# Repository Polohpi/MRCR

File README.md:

# MRCR
Banc de Rodage pour moteur Nitro

Arduino SAMD21 M0

using :

PID_v1 library            https://github.com/br3ttb/Arduino-PID-Library
Scheduler                 https://github.com/arduino-libraries/Scheduler
Easy Nextion Library      https://github.com/Seithan/EasyNextionLibrary
MovingAvg                  https://github.com/JChristensen/movingAvg

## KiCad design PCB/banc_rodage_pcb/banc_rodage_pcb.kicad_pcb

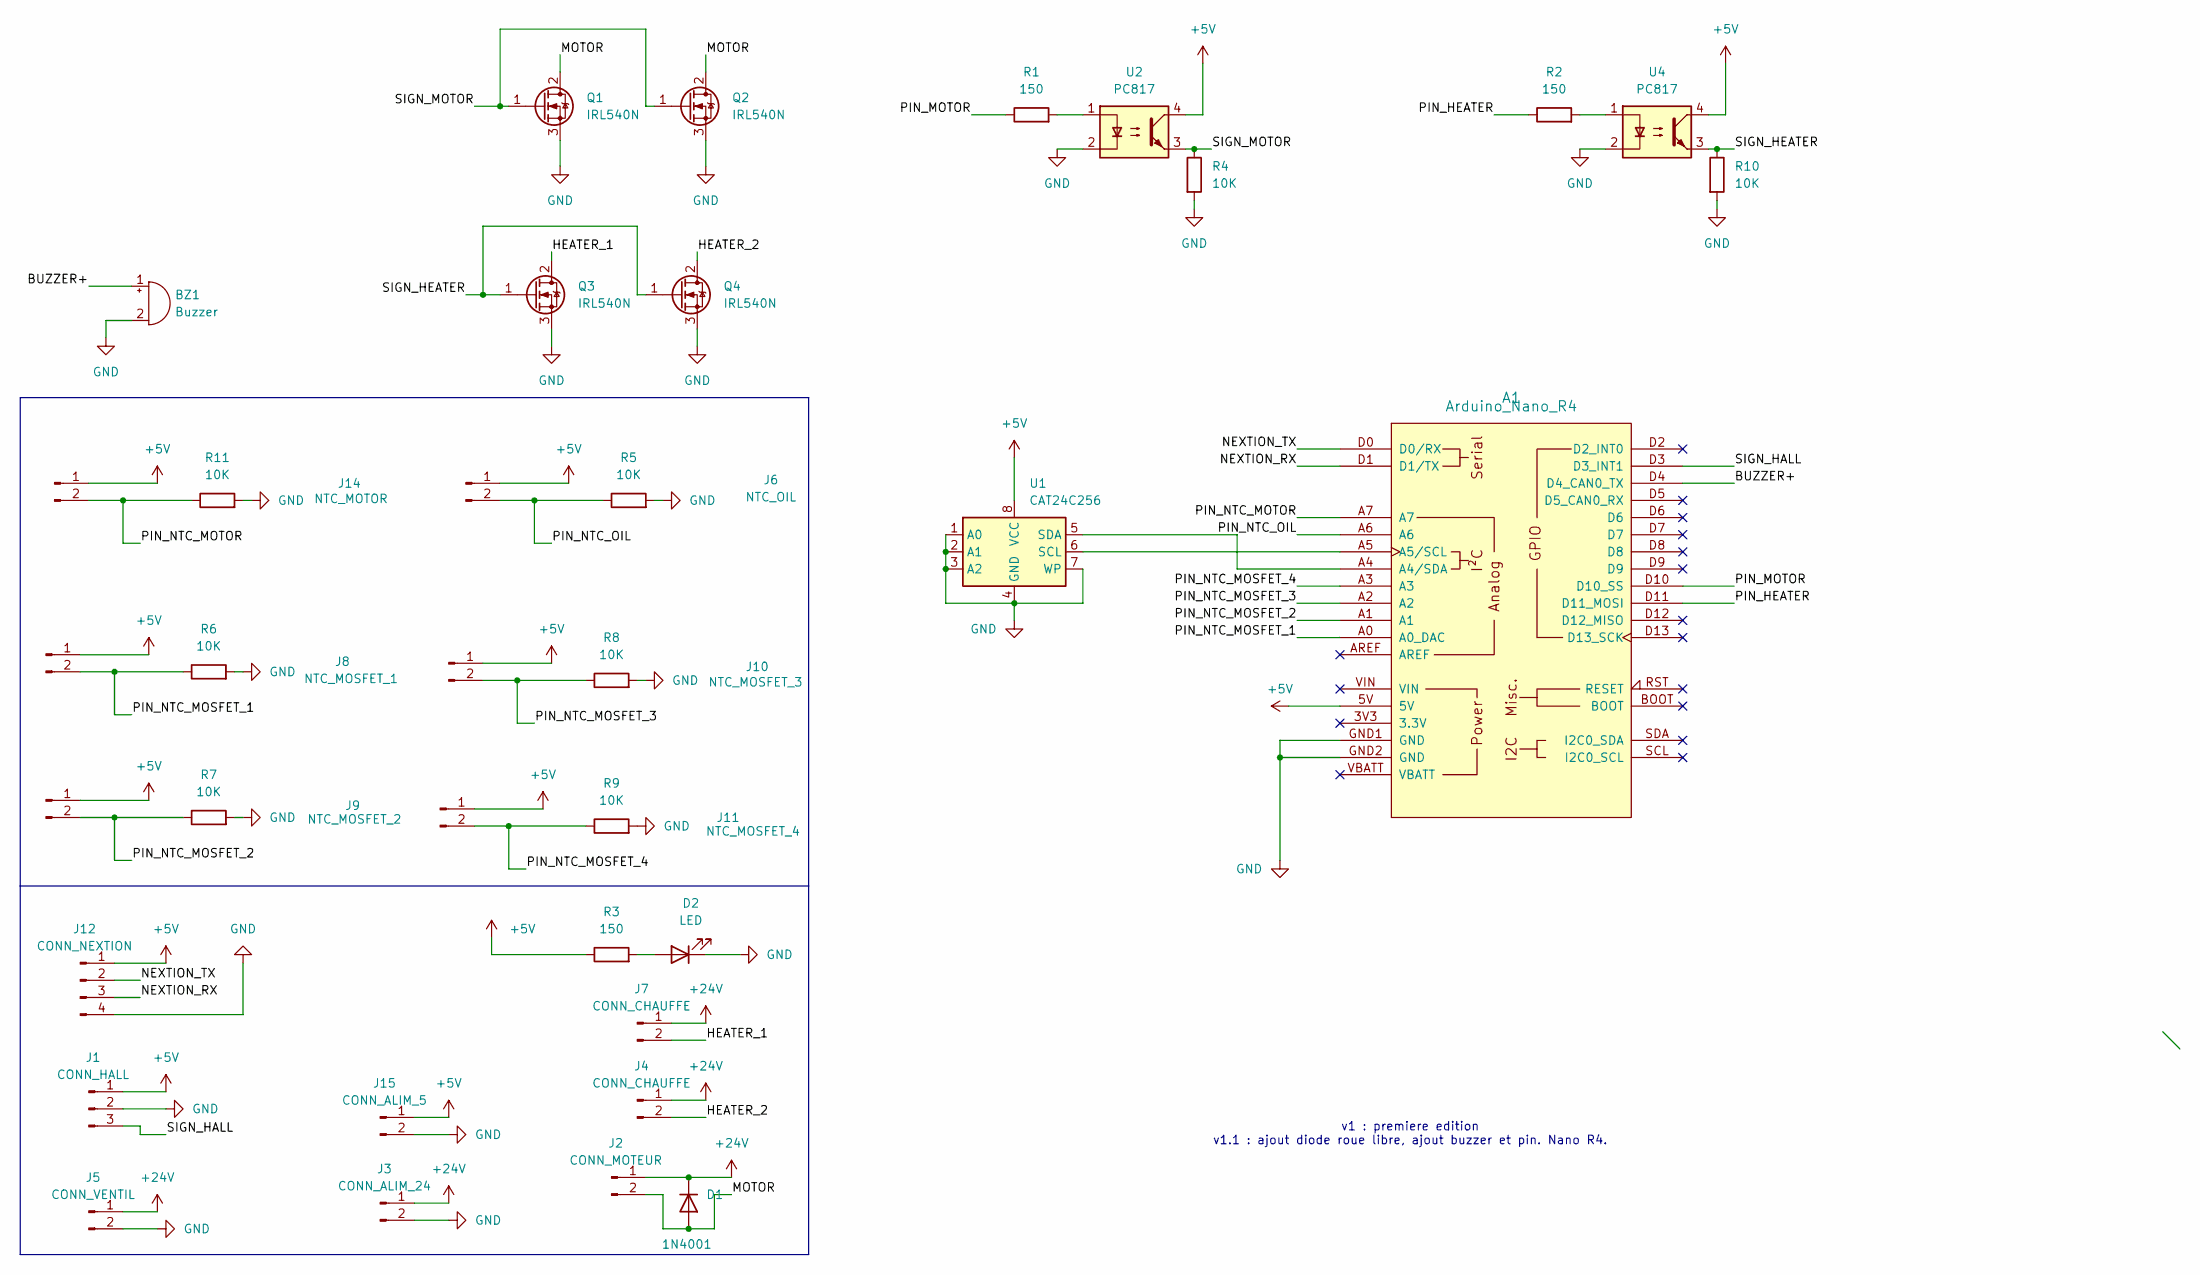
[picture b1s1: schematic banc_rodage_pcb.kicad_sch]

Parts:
A1: Arduino_Nano_R4
BZ1: Buzzer; Buzzer_12x9.5RM7.6
D1: 1N4001; D_DO-41_SOD81_P10.16mm_Horizontal
D2: LED; LED_D3.0mm
J1: CONN_HALL; JST_XH_B3B-XH-A_1x03_P2.50mm_Vertical
J2: CONN_MOTEUR; TerminalBlock_bornier-2_P5.08mm
J3: CONN_ALIM_24; TerminalBlock_bornier-2_P5.08mm
J4, J7: CONN_CHAUFFE; TerminalBlock_bornier-2_P5.08mm
J5: CONN_VENTIL; JST_XH_B2B-XH-A_1x02_P2.50mm_Vertical
J6: NTC_OIL; JST_XH_B2B-XH-A_1x02_P2.50mm_Vertical
J8: NTC_MOSFET_1; JST_XH_B2B-XH-A_1x02_P2.50mm_Vertical
J9: NTC_MOSFET_2; JST_XH_B2B-XH-A_1x02_P2.50mm_Vertical
J10: NTC_MOSFET_3; JST_XH_B2B-XH-A_1x02_P2.50mm_Vertical
J11: NTC_MOSFET_4; JST_XH_B2B-XH-A_1x02_P2.50mm_Vertical
J12: CONN_NEXTION; JST_XH_B4B-XH-A_1x04_P2.50mm_Vertical
J14: NTC_MOTOR; JST_XH_B2B-XH-A_1x02_P2.50mm_Vertical
J15: CONN_ALIM_5; TerminalBlock_bornier-2_P5.08mm
Q1, Q2, Q3, Q4: IRL540N; TO-220F-3_Horizontal_TabUp
R1, R2, R3: 150; R_1206_3216Metric
R4, R5, R6, R7, R8, R9, R10, R11: 10K; R_1206_3216Metric
U1: CAT24C256; DIP-8_W7.62mm_Socket
U2, U4: PC817; DIP-4_W7.62mm

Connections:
+5V: A1.5V, J1.1, J6.1, J8.1, J9.1, J10.1, J11.1, J12.1, J14.1, J15.1, R3.1, U1.8 (VCC), U2.4, U4.4
+24V: D1.1 (K), J2.1, J3.1, J4.1, J5.1, J7.1
/BUZZER+: A1.D4 (D4_CAN0_TX), BZ1.1 (+)
/HEATER_1: J7.2, Q3.2 (D)
/HEATER_2: J4.2, Q4.2 (D)
/MOTOR: D1.2 (A), J2.2, Q1.2 (D), Q2.2 (D)
/NEXTION_RX: A1.D1 (D1/TX), J12.3
/NEXTION_TX: A1.D0 (D0/RX), J12.2
/PIN_HEATER: A1.D11 (D11_MOSI), R2.1
/PIN_MOTOR: A1.D10 (D10_SS), R1.1
/PIN_NTC_MOSFET_1: A1.A0 (A0_DAC), J8.2, R6.1
/PIN_NTC_MOSFET_2: A1.A1, J9.2, R7.1
/PIN_NTC_MOSFET_3: A1.A2, J10.2, R8.1
/PIN_NTC_MOSFET_4: A1.A3, J11.2, R9.1
/PIN_NTC_MOTOR: A1.A7, J14.2, R11.1
/PIN_NTC_OIL: A1.A6, J6.2, R5.1
/SIGN_HALL: A1.D3 (D3_INT1), J1.3
/SIGN_HEATER: Q3.1 (G), Q4.1 (G), R10.1, U4.3
/SIGN_MOTOR: Q1.1 (G), Q2.1 (G), R4.1, U2.3
GND: A1.GND1 (GND), A1.GND2 (GND), BZ1.2 (-), D2.1 (K), J1.2, J3.2, J5.2, J12.4, J15.2, Q1.3 (S), Q2.3 (S), Q3.3 (S), Q4.3 (S), R4.2, R5.2, R6.2, R7.2, R8.2, R9.2, R10.2, R11.2, U1.1 (A0), U1.2 (A1), U1.3 (A2), U1.4 (GND), U1.7 (WP), U2.2, U4.2
unnamed: A1.A4 (A4/SDA), U1.5 (SDA)
unnamed: A1.A5 (A5/SCL), U1.6 (SCL)
unnamed: D2.2 (A), R3.2
unnamed: R1.2, U2.1
unnamed: R2.2, U4.1

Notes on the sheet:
v1 : premiere edition v1.1 : ajout diode roue libre, ajout buzzer et pin. Nano R4.

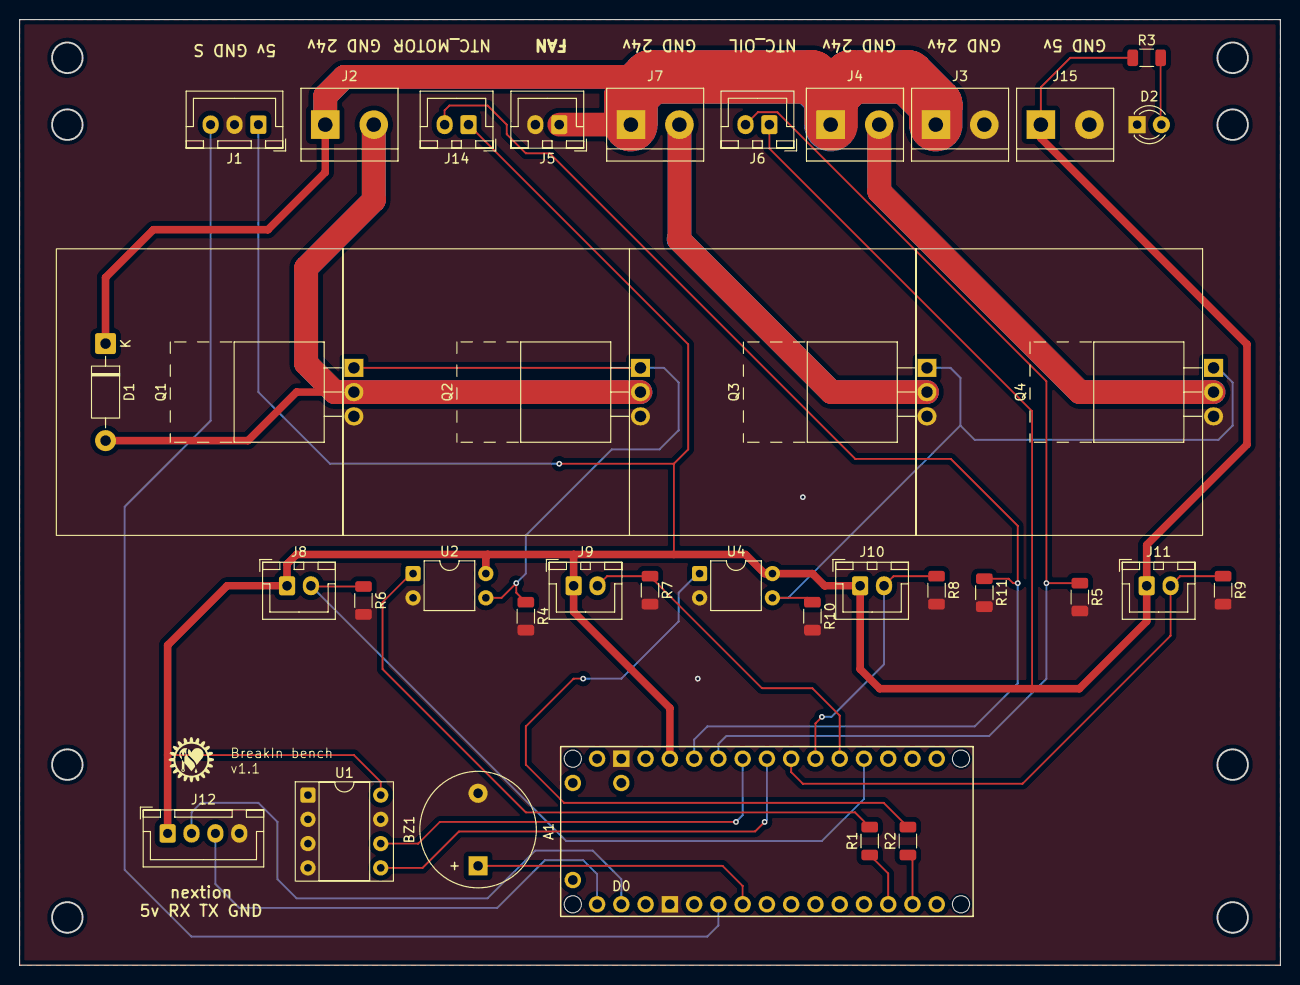
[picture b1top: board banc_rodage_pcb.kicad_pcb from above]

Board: 2 copper layers, 131.9 x 98.9 mm, 36 parts (0 on the bottom side), 25 nets.

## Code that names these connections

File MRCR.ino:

#include "lib_variable.h"
#include "function_software.h"
#include "function_hardware.h"
#include "page.h"
#include "function_nextion.h"



void setup() {
  
  analogWriteResolution(12); //14 because 16 make the PID and the motor very very long to respond
  Serial.begin(9600);
  Nextion.begin(9600); // Begin the object with a baud rate of 9600


  Serial.println("Setup");
  Scheduler.startLoop(ntc_update);
  Scheduler.startLoop(backend_nextion);
  Scheduler.startLoop(MOTOR_PID);
  Scheduler.startLoop(RPM_update);
  Scheduler.startLoop(HEAT_ramp);
  Scheduler.startLoop(debug, 2048);
  Scheduler.startLoop(Manual_Timer);
  Scheduler.startLoop(Security);
  Scheduler.startLoop(MainPage);
  Scheduler.startLoop(ManualModePage);


  Motor_PID.SetMode(AUTOMATIC);

  Motor_PID.SetOutputLimits(0, 6700); //see backend_PID()
  
  Avg_Temp_ntc_oil.begin(); // start movingavg for heating, motor and ntc sensor
  Avg_MotorRPM.begin();
  Avg_Temp_ntc_mosfet_motor_1.begin();
  Avg_Temp_ntc_mosfet_motor_2.begin();
  Avg_Temp_ntc_motor.begin();
  Avg_Temp_ntc_mosfet_heat_1.begin();
  Avg_Temp_ntc_mosfet_heat_2.begin();
  Avg_MotorRPM.reset();

  pinMode(PIN_NTC_MOSFET_MOTOR_1, INPUT);      // set pinmode
  pinMode(PIN_NTC_MOSFET_MOTOR_2, INPUT);
  pinMode(PIN_NTC_MOSFET_HEAT_1, INPUT);
  pinMode(PIN_NTC_MOSFET_HEAT_2, INPUT);
  pinMode(PIN_NTC_MOTOR, INPUT); //pullup here to avaoid erratic reaing before the pcb v2 wich will include a ntc sensor for the DC motor itself
  pinMode(PIN_NTC_OIL, INPUT);
  pinMode(PIN_MOTOR, OUTPUT);
  pinMode(PIN_HEATER, OUTPUT); 
  pinMode(PIN_IR_SENSOR, INPUT_PULLUP);

  attachInterrupt(digitalPinToInterrupt(PIN_IR_SENSOR), RPM_interrupt, FALLING);
  yield();
  delay(2000);
}

void loop() 
{

  if(MAIN_PAGE == false && MANUAL_MODE_PAGE == false)
  {
  Nextion.writeStr("page Main");
  MAIN_PAGE = true;
  }
  yield();
}

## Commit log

2024-11-16 base pour reprog samd21
2024-11-24 cleaning
2024-11-28 scheduler + NTC
    implementation from scratch of the NTC temp sensor and the first scheduler loop
2025-08-05 Backups are important. Bitlocker is not your friend sometimes.
2025-08-08 PID motor in progress but not finished. Nextion and NTC OK
2025-08-08 working motor PID
2025-08-09 Added Kicad Files. Addes many page for the menu. Work in progress
2025-08-11 add a debug loop. Start working on the heating PIDs. Nextion : moving the the 4.3 inch screen. Started Settings menu to set the Nextion RTC. Started diagnostic menus with sensors values. Global look 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
2025-08-12 starting moving to an nano R4 RA4M1
2025-08-13 working motor PID on the R4. Keep pushing paul keep pushing.
2025-08-13 heater controls OK using a simple ON OFF system
2025-08-16 cleanup. automode : gestion of brenkin profile with the sd card (rename, duplicate, delete) is ok
2025-08-19 modifiy the selection of files. Add a common keyboard.
2025-08-29 pcb v1.1 validated. every things works as expected. New screen received. keep pushing keep pushing
2025-12-07 added timer function for the manual mode
2025-12-07 global cleanup. Simplified the variable name for the nextion.
2025-12-07 added basic security functions. rework of the way pages are handle. no more loop in other loop. Everyhting works with true false flags. all pages are now executed with scheduler loop
